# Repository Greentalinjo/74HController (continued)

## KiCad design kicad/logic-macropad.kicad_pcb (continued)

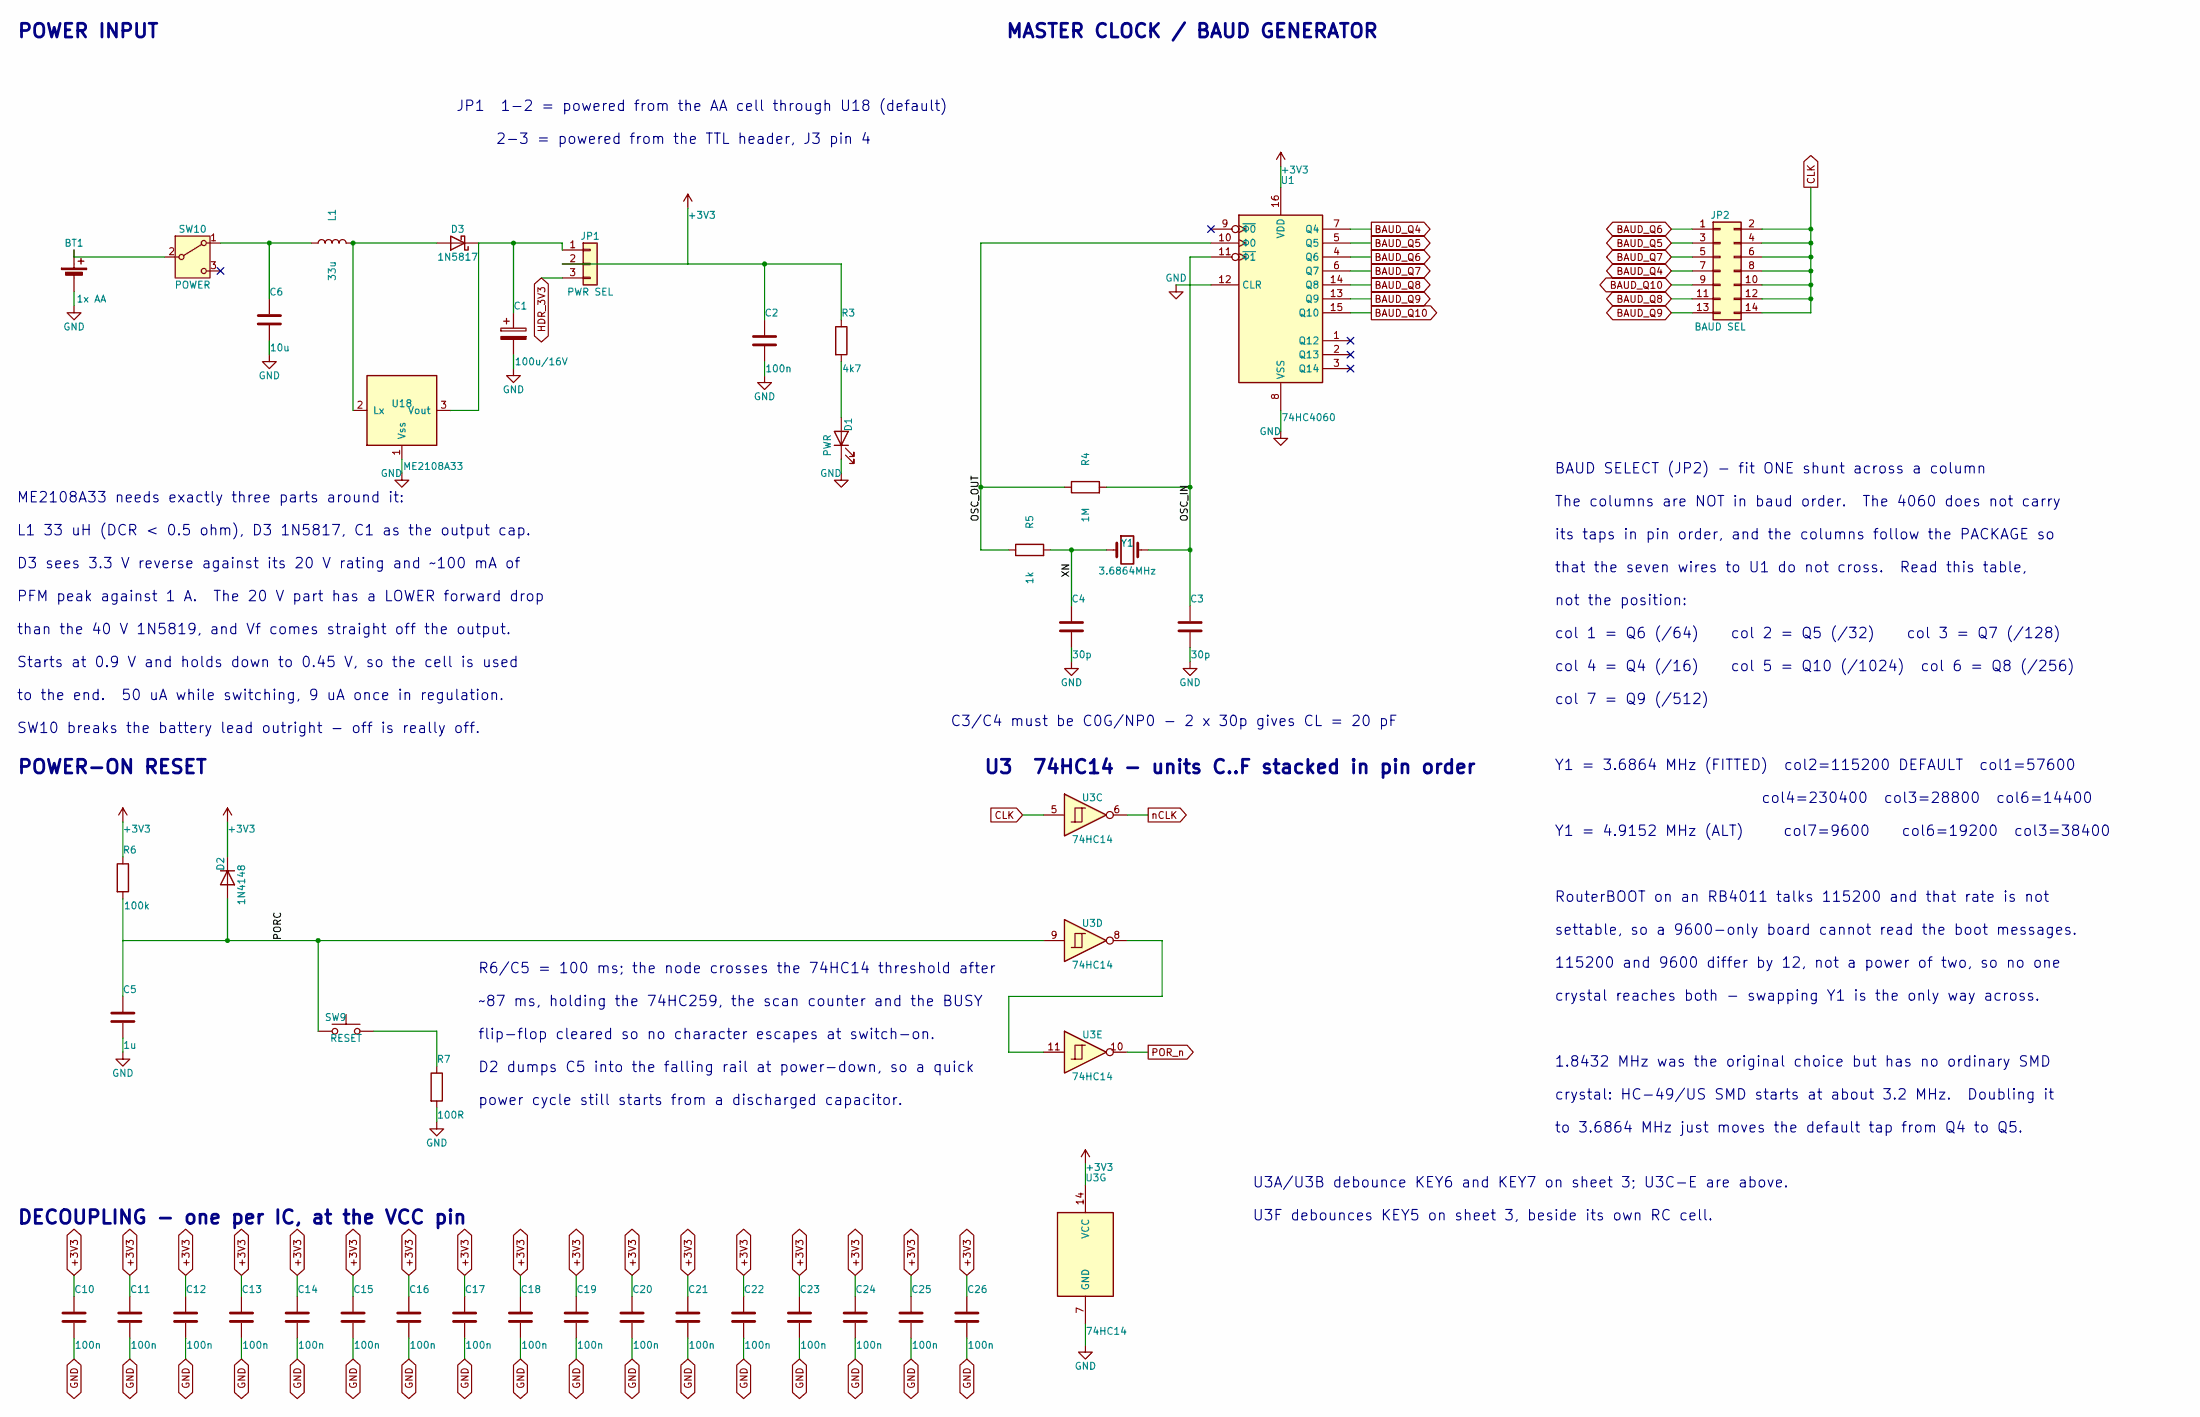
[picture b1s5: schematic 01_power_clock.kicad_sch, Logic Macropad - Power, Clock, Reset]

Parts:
BT1: 1x AA; BatteryHolder_MYOUNG_BH-AA-A1AJ020_1xAA; MPN BH-AA-A1AJ020
C1: 100u/16V; CP_Radial_D5.0mm_P2.00mm; MPN UVR1C101MED
C2, C10, C11, C12, C13, C14, C15, C16, C17, C18, C19, C20, C21, C22, C23, C24, C25, C26: 100n; C_0402_1005Metric; MPN GRM155R71H104KE14D
C3, C4: 30p; C_0402_1005Metric; MPN CC0402JRNPO9BN300
C5: 1u; C_0805_2012Metric; MPN GRM21BR71H105KA12L
C6: 10u; C_0805_2012Metric
D1: PWR; LED_0805_2012Metric_Pad1.15x1.40mm_HandSolder
D2: 1N4148; D_SOD-523; MPN 1N4148WT-7
D3: 1N5817; D_DO-41_SOD81_P10.16mm_Horizontal
JP1: PWR SEL; PinHeader_1x03_P2.54mm_Vertical; MPN 2.54-1*40P
JP2: BAUD SEL; PinHeader_2x07_P2.54mm_Vertical; MPN 2.54-2*7P
L1: 33u; L_Cenker_CKCS5040
R3: 4k7; R_0603_1608Metric
R4: 1M; R_0603_1608Metric
R5: 1k; R_0603_1608Metric
R6: 100k; R_0603_1608Metric
R7: 100R; R_0603_1608Metric
SW9: RESET; SW_PUSH_6mm; MPN K2-1102DP-F4SW-04
SW10: POWER; SW_Toggle_SPDT_ST-0-102; MPN ST-0-102-A01-T000-LF
U1: 74HC4060; SOIC-16_3.9x9.9mm_P1.27mm; MPN 74HC4060D
U3: 74HC14; SOIC-14_3.9x8.7mm_P1.27mm; MPN 74HC14D
U18: ME2108A33; SOT-23; MPN ME2108A33M3G
Y1: 3.6864MHz; Crystal_SMD_HC49-SD_HandSoldering; MPN ABLS-3.6864MHZ-B4-T

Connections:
+3V3: C2.1, C10.1, C11.1, C12.1, C13.1, C14.1, C15.1, C16.1, C17.1, C18.1, C19.1, C20.1, C21.1, C22.1, C23.1, C24.1, C25.1, C26.1, D2.1 (K), JP1.2, R3.1, R6.1, U1.16 (VDD), U3.14 (VCC); also elsewhere on the board
/Power, Clock, Reset/OSC_IN: C3.1, R4.2, U1.11 (~Φ1), Y1.2
/Power, Clock, Reset/OSC_OUT: R4.1, R5.1, U1.10 (Φ0)
/Power, Clock, Reset/PORC: C5.1, D2.2 (A), R6.2, SW9.1, U3.9
/Power, Clock, Reset/XN: C4.1, R5.2, Y1.1
BAUD_Q4: JP2.7, U1.7 (Q4)
BAUD_Q5: JP2.3, U1.5 (Q5)
BAUD_Q6: JP2.1, U1.4 (Q6)
BAUD_Q7: JP2.5, U1.6 (Q7)
BAUD_Q8: JP2.11, U1.14 (Q8)
BAUD_Q9: JP2.13, U1.13 (Q9)
BAUD_Q10: JP2.9, U1.15 (Q10)
CLK: JP2.2, JP2.4, JP2.6, JP2.8, JP2.10, JP2.12, JP2.14, U3.5; also elsewhere on the board
GND: BT1.2 (-), C1.2, C2.2, C3.2, C4.2, C5.2, C6.2, C10.2, C11.2, C12.2, C13.2, C14.2, C15.2, C16.2, C17.2, C18.2, C19.2, C20.2, C21.2, C22.2, C23.2, C24.2, C25.2, C26.2, D1.1 (K), R7.2, U1.8 (VSS), U1.12 (CLR), U3.7 (GND), U18.1 (Vss); also elsewhere on the board
HDR_3V3: JP1.3; also elsewhere on the board
unnamed: BT1.1 (+), SW10.2 (B)
unnamed: D1.2 (A), R3.2
unnamed: D3.2 (A), L1.2, U18.2 (Lx)
unnamed: C1.1, D3.1 (K), JP1.1, U18.3 (Vout)
unnamed: R7.1, SW9.2
unnamed: C6.1, L1.1, SW10.1 (A)
unnamed: U3.8, U3.11
POR_n: U3.10; also elsewhere on the board
nCLK: U3.6; also elsewhere on the board

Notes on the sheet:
flip-flop cleared so no character escapes at switch-on.
1.8432 MHz was the original choice but has no ordinary SMD
than the 40 V 1N5819, and Vf comes straight off the output.
col4=230400 col3=28800 col6=14400
settable, so a 9600-only board cannot read the boot messages.
Y1 = 3.6864 MHz (FITTED) col2=115200 DEFAULT col1=57600
crystal reaches both - swapping Y1 is the only way across.
POWER INPUT
The columns are NOT in baud order. The 4060 does not carry
col 4 = Q4 (/16) col 5 = Q10 (/1024) col 6 = Q8 (/256)
Starts at 0.9 V and holds down to 0.45 V, so the cell is used
its taps in pin order, and the columns follow the PACKAGE so
D3 sees 3.3 V reverse against its 20 V rating and ~100 mA of
R6/C5 = 100 ms; the node crosses the 74HC14 threshold after
not the position:
U3A/U3B debounce KEY6 and KEY7 on sheet 3; U3C-E are above.
col 7 = Q9 (/512)
2-3 = powered from the TTL header, J3 pin 4
BAUD SELECT (JP2) - fit ONE shunt across a column
Y1 = 4.9152 MHz (ALT) col7=9600 col6=19200 col3=38400
115200 and 9600 differ by 12, not a power of two, so no one
U3F debounces KEY5 on sheet 3, beside its own RC cell.
POWER-ON RESET
power cycle still starts from a discharged capacitor.
to the end. 50 uA while switching, 9 uA once in regulation.
PFM peak against 1 A. The 20 V part has a LOWER forward drop
U3 74HC14 - units C..F stacked in pin order
ME2108A33 needs exactly three parts around it:
C3/C4 must be C0G/NP0 - 2 x 30p gives CL = 20 pF
D2 dumps C5 into the falling rail at power-down, so a quick
MASTER CLOCK / BAUD GENERATOR
DECOUPLING - one per IC, at the VCC pin
to 3.6864 MHz just moves the default tap from Q4 to Q5.
SW10 breaks the battery lead outright - off is really off.
RouterBOOT on an RB4011 talks 115200 and that rate is not
JP1 1-2 = powered from the AA cell through U18 (default)
L1 33 uH (DCR < 0.5 ohm), D3 1N5817, C1 as the output cap.
that the seven wires to U1 do not cross. Read this table,
col 1 = Q6 (/64) col 2 = Q5 (/32) col 3 = Q7 (/128)
crystal: HC-49/US SMD starts at about 3.2 MHz. Doubling it

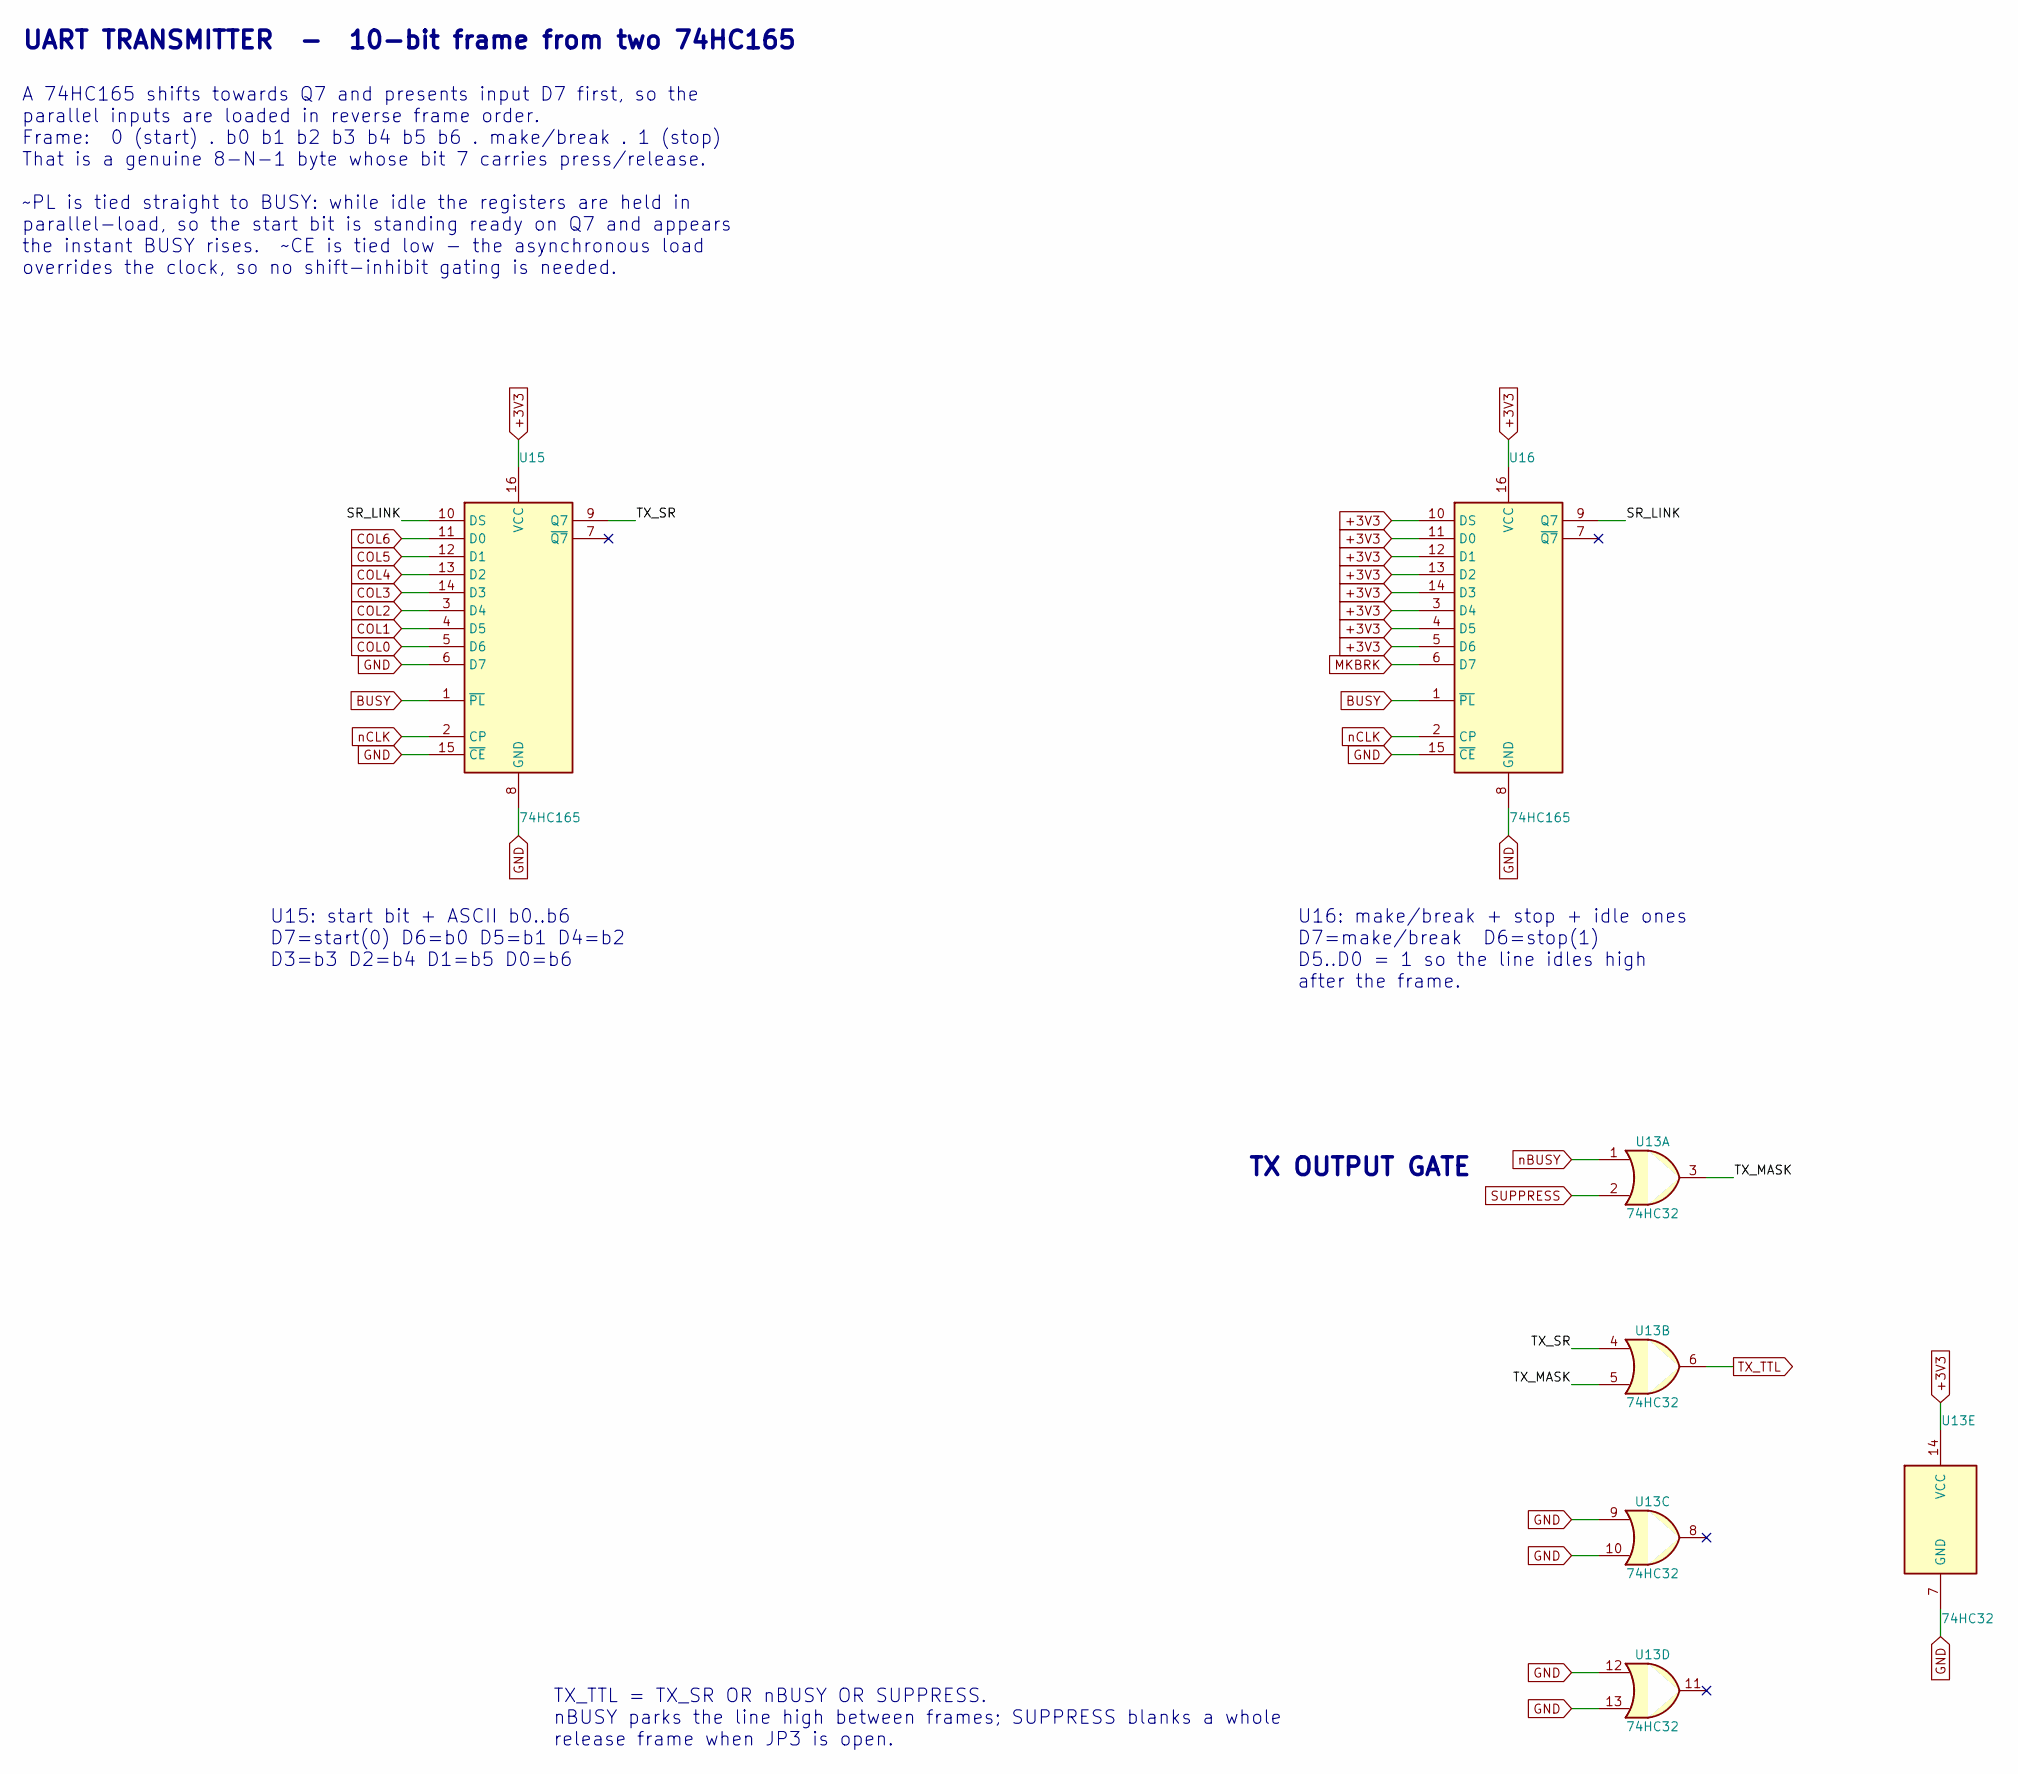
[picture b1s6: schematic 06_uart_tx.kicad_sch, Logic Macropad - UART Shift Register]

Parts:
U13: 74HC32; SOIC-14_3.9x8.7mm_P1.27mm; MPN 74HC32D
U15, U16: 74HC165; SOIC-16_3.9x9.9mm_P1.27mm; MPN 74HC165D

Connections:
+3V3: U13.14 (VCC), U15.16 (VCC), U16.3 (D4), U16.4 (D5), U16.5 (D6), U16.10 (DS), U16.11 (D0), U16.12 (D1), U16.13 (D2), U16.14 (D3), U16.16 (VCC); also elsewhere on the board
/UART Shift Register/SR_LINK: U15.10 (DS), U16.9 (Q7)
/UART Shift Register/TX_MASK: U13.3, U13.5
/UART Shift Register/TX_SR: U13.4, U15.9 (Q7)
BUSY: U15.1 (~PL), U16.1 (~PL); also elsewhere on the board
COL0: U15.5 (D6); also elsewhere on the board
COL1: U15.4 (D5); also elsewhere on the board
COL2: U15.3 (D4); also elsewhere on the board
COL3: U15.14 (D3); also elsewhere on the board
COL4: U15.13 (D2); also elsewhere on the board
COL5: U15.12 (D1); also elsewhere on the board
COL6: U15.11 (D0); also elsewhere on the board
GND: U13.7 (GND), U13.9, U13.10, U13.12, U13.13, U15.6 (D7), U15.8 (GND), U15.15 (~CE), U16.8 (GND), U16.15 (~CE); also elsewhere on the board
MKBRK: U16.6 (D7); also elsewhere on the board
SUPPRESS: U13.2; also elsewhere on the board
TX_TTL: U13.6; also elsewhere on the board
nBUSY: U13.1; also elsewhere on the board
nCLK: U15.2 (CP), U16.2 (CP); also elsewhere on the board

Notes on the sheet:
A 74HC165 shifts towards Q7 and presents input D7 first, so the parallel inputs are loaded in reverse frame order. Frame: 0 (start) . b0 b1 b2 b3 b4 b5 b6 . make/break . 1 (stop) That is a genuine 8-N-1 byte whose bit 7 carries press/release. ~PL is tied straight to BUSY: while idle the registers a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
UART TRANSMITTER - 10-bit frame from two 74HC165
TX_TTL = TX_SR OR nBUSY OR SUPPRESS. nBUSY parks the line high between frames; SUPPRESS blanks a whole release frame when JP3 is open.
U15: start bit + ASCII b0..b6 D7=start(0) D6=b0 D5=b1 D4=b2 D3=b3 D2=b4 D1=b5 D0=b6
U16: make/break + stop + idle ones D7=make/break D6=stop(1) D5..D0 = 1 so the line idles high after the frame.
TX OUTPUT GATE

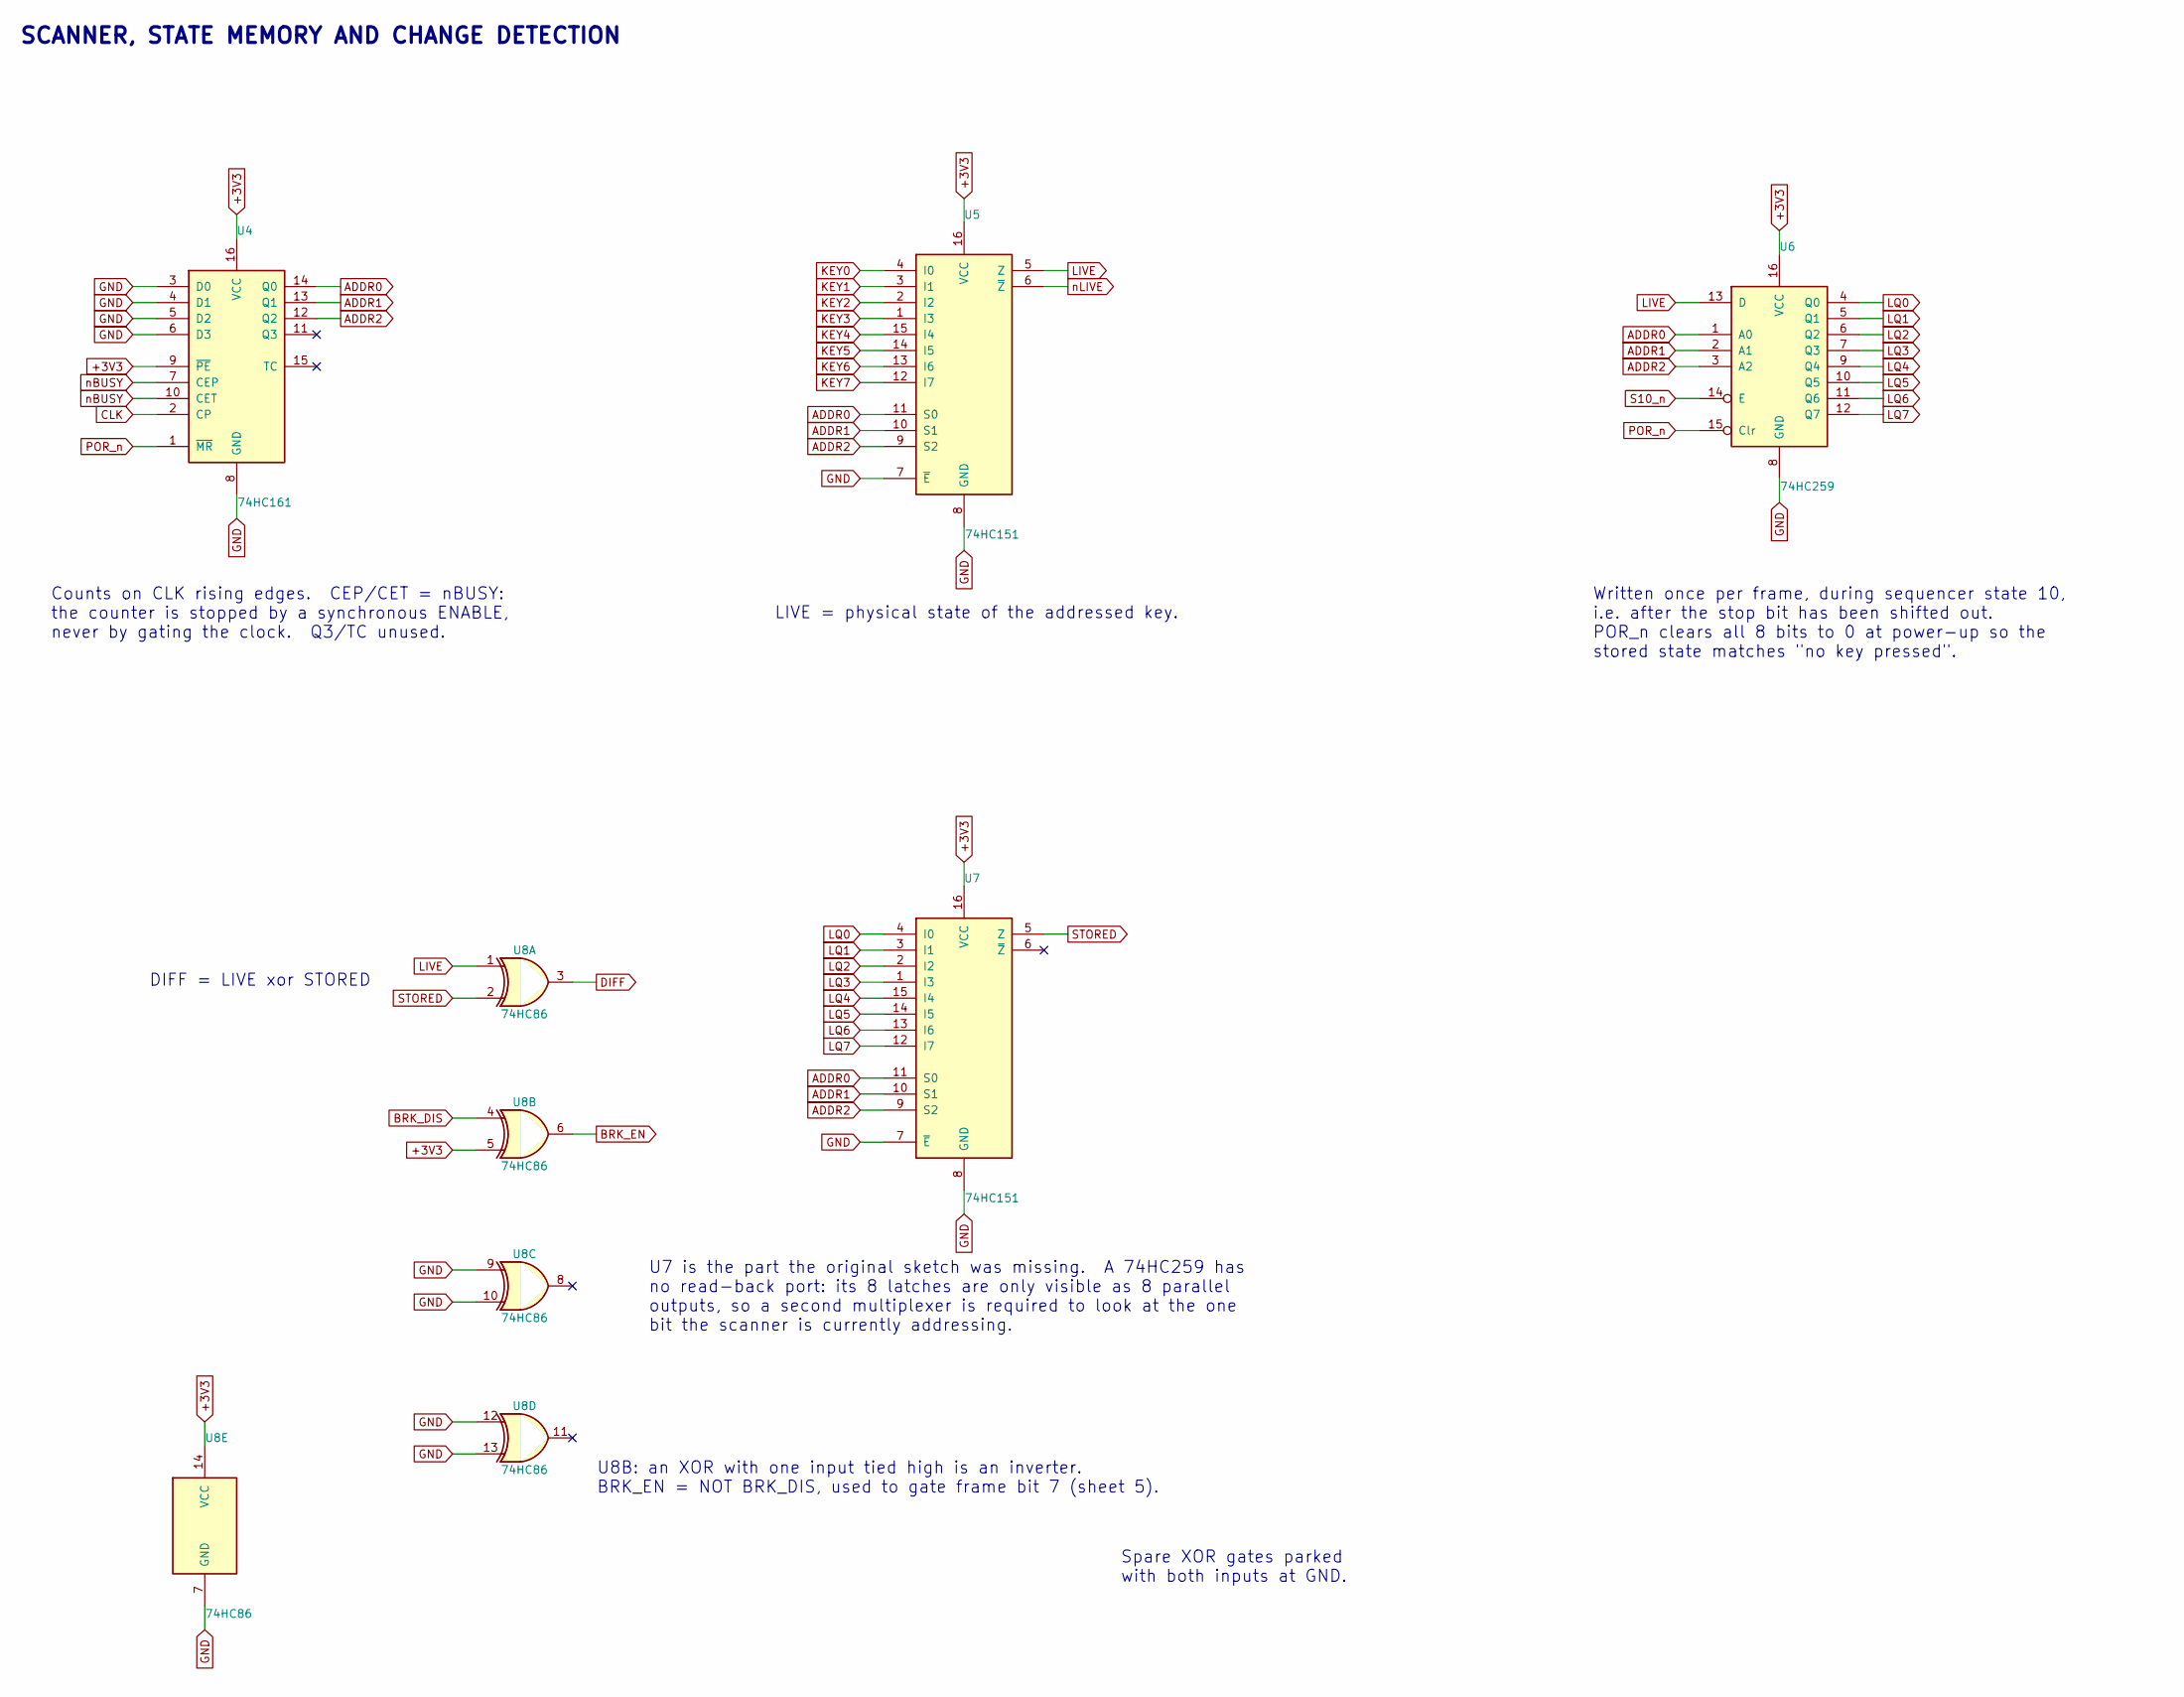
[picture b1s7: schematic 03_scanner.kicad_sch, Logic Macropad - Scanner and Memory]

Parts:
U4: 74HC161; SOIC-16_3.9x9.9mm_P1.27mm; MPN 74HC161D
U5, U7: 74HC151; SOIC-16_3.9x9.9mm_P1.27mm; MPN 74HC151D
U6: 74HC259; SOIC-16_3.9x9.9mm_P1.27mm; MPN 74HC259D
U8: 74HC86; SOIC-14_3.9x8.7mm_P1.27mm; MPN 74HC86D

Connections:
+3V3: U4.9 (~PE), U4.16 (VCC), U5.16 (VCC), U6.16 (VCC), U7.16 (VCC), U8.5, U8.14 (VCC); also elsewhere on the board
ADDR0: U4.14 (Q0), U5.11 (S0), U6.1 (A0), U7.11 (S0); also elsewhere on the board
ADDR1: U4.13 (Q1), U5.10 (S1), U6.2 (A1), U7.10 (S1); also elsewhere on the board
ADDR2: U4.12 (Q2), U5.9 (S2), U6.3 (A2), U7.9 (S2); also elsewhere on the board
BRK_DIS: U8.4; also elsewhere on the board
BRK_EN: U8.6; also elsewhere on the board
CLK: U4.2 (CP); also elsewhere on the board
DIFF: U8.3; also elsewhere on the board
GND: U4.3 (D0), U4.4 (D1), U4.5 (D2), U4.6 (D3), U4.8 (GND), U5.7 (~E), U5.8 (GND), U6.8 (GND), U7.7 (~E), U7.8 (GND), U8.7 (GND), U8.9, U8.10, U8.12, U8.13; also elsewhere on the board
KEY0: U5.4 (I0); also elsewhere on the board
KEY1: U5.3 (I1); also elsewhere on the board
KEY2: U5.2 (I2); also elsewhere on the board
KEY3: U5.1 (I3); also elsewhere on the board
KEY4: U5.15 (I4); also elsewhere on the board
KEY5: U5.14 (I5); also elsewhere on the board
KEY6: U5.13 (I6); also elsewhere on the board
KEY7: U5.12 (I7); also elsewhere on the board
LIVE: U5.5 (Z), U6.13 (D), U8.1; also elsewhere on the board
LQ0: U6.4 (Q0), U7.4 (I0)
LQ1: U6.5 (Q1), U7.3 (I1)
LQ2: U6.6 (Q2), U7.2 (I2)
LQ3: U6.7 (Q3), U7.1 (I3)
LQ4: U6.9 (Q4), U7.15 (I4)
LQ5: U6.10 (Q5), U7.14 (I5)
LQ6: U6.11 (Q6), U7.13 (I6)
LQ7: U6.12 (Q7), U7.12 (I7)
POR_n: U4.1 (~MR), U6.15 (Clr); also elsewhere on the board
S10_n: U6.14 (E); also elsewhere on the board
STORED: U7.5 (Z), U8.2
nBUSY: U4.7 (CEP), U4.10 (CET); also elsewhere on the board
nLIVE: U5.6 (~Z); also elsewhere on the board

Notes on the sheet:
LIVE = physical state of the addressed key.
DIFF = LIVE xor STORED
Spare XOR gates parked with both inputs at GND.
Counts on CLK rising edges. CEP/CET = nBUSY: the counter is stopped by a synchronous ENABLE, never by gating the clock. Q3/TC unused.
U8B: an XOR with one input tied high is an inverter. BRK_EN = NOT BRK_DIS, used to gate frame bit 7 (sheet 5).
SCANNER, STATE MEMORY AND CHANGE DETECTION
U7 is the part the original sketch was missing. A 74HC259 has no read-back port: its 8 latches are only visible as 8 parallel outputs, so a second multiplexer is required to look at the one bit the scanner is currently addressing.
Written once per frame, during sequencer state 10, i.e. after the stop bit has been shifted out. POR_n clears all 8 bits to 0 at power-up so the stored state matches "no key pressed".

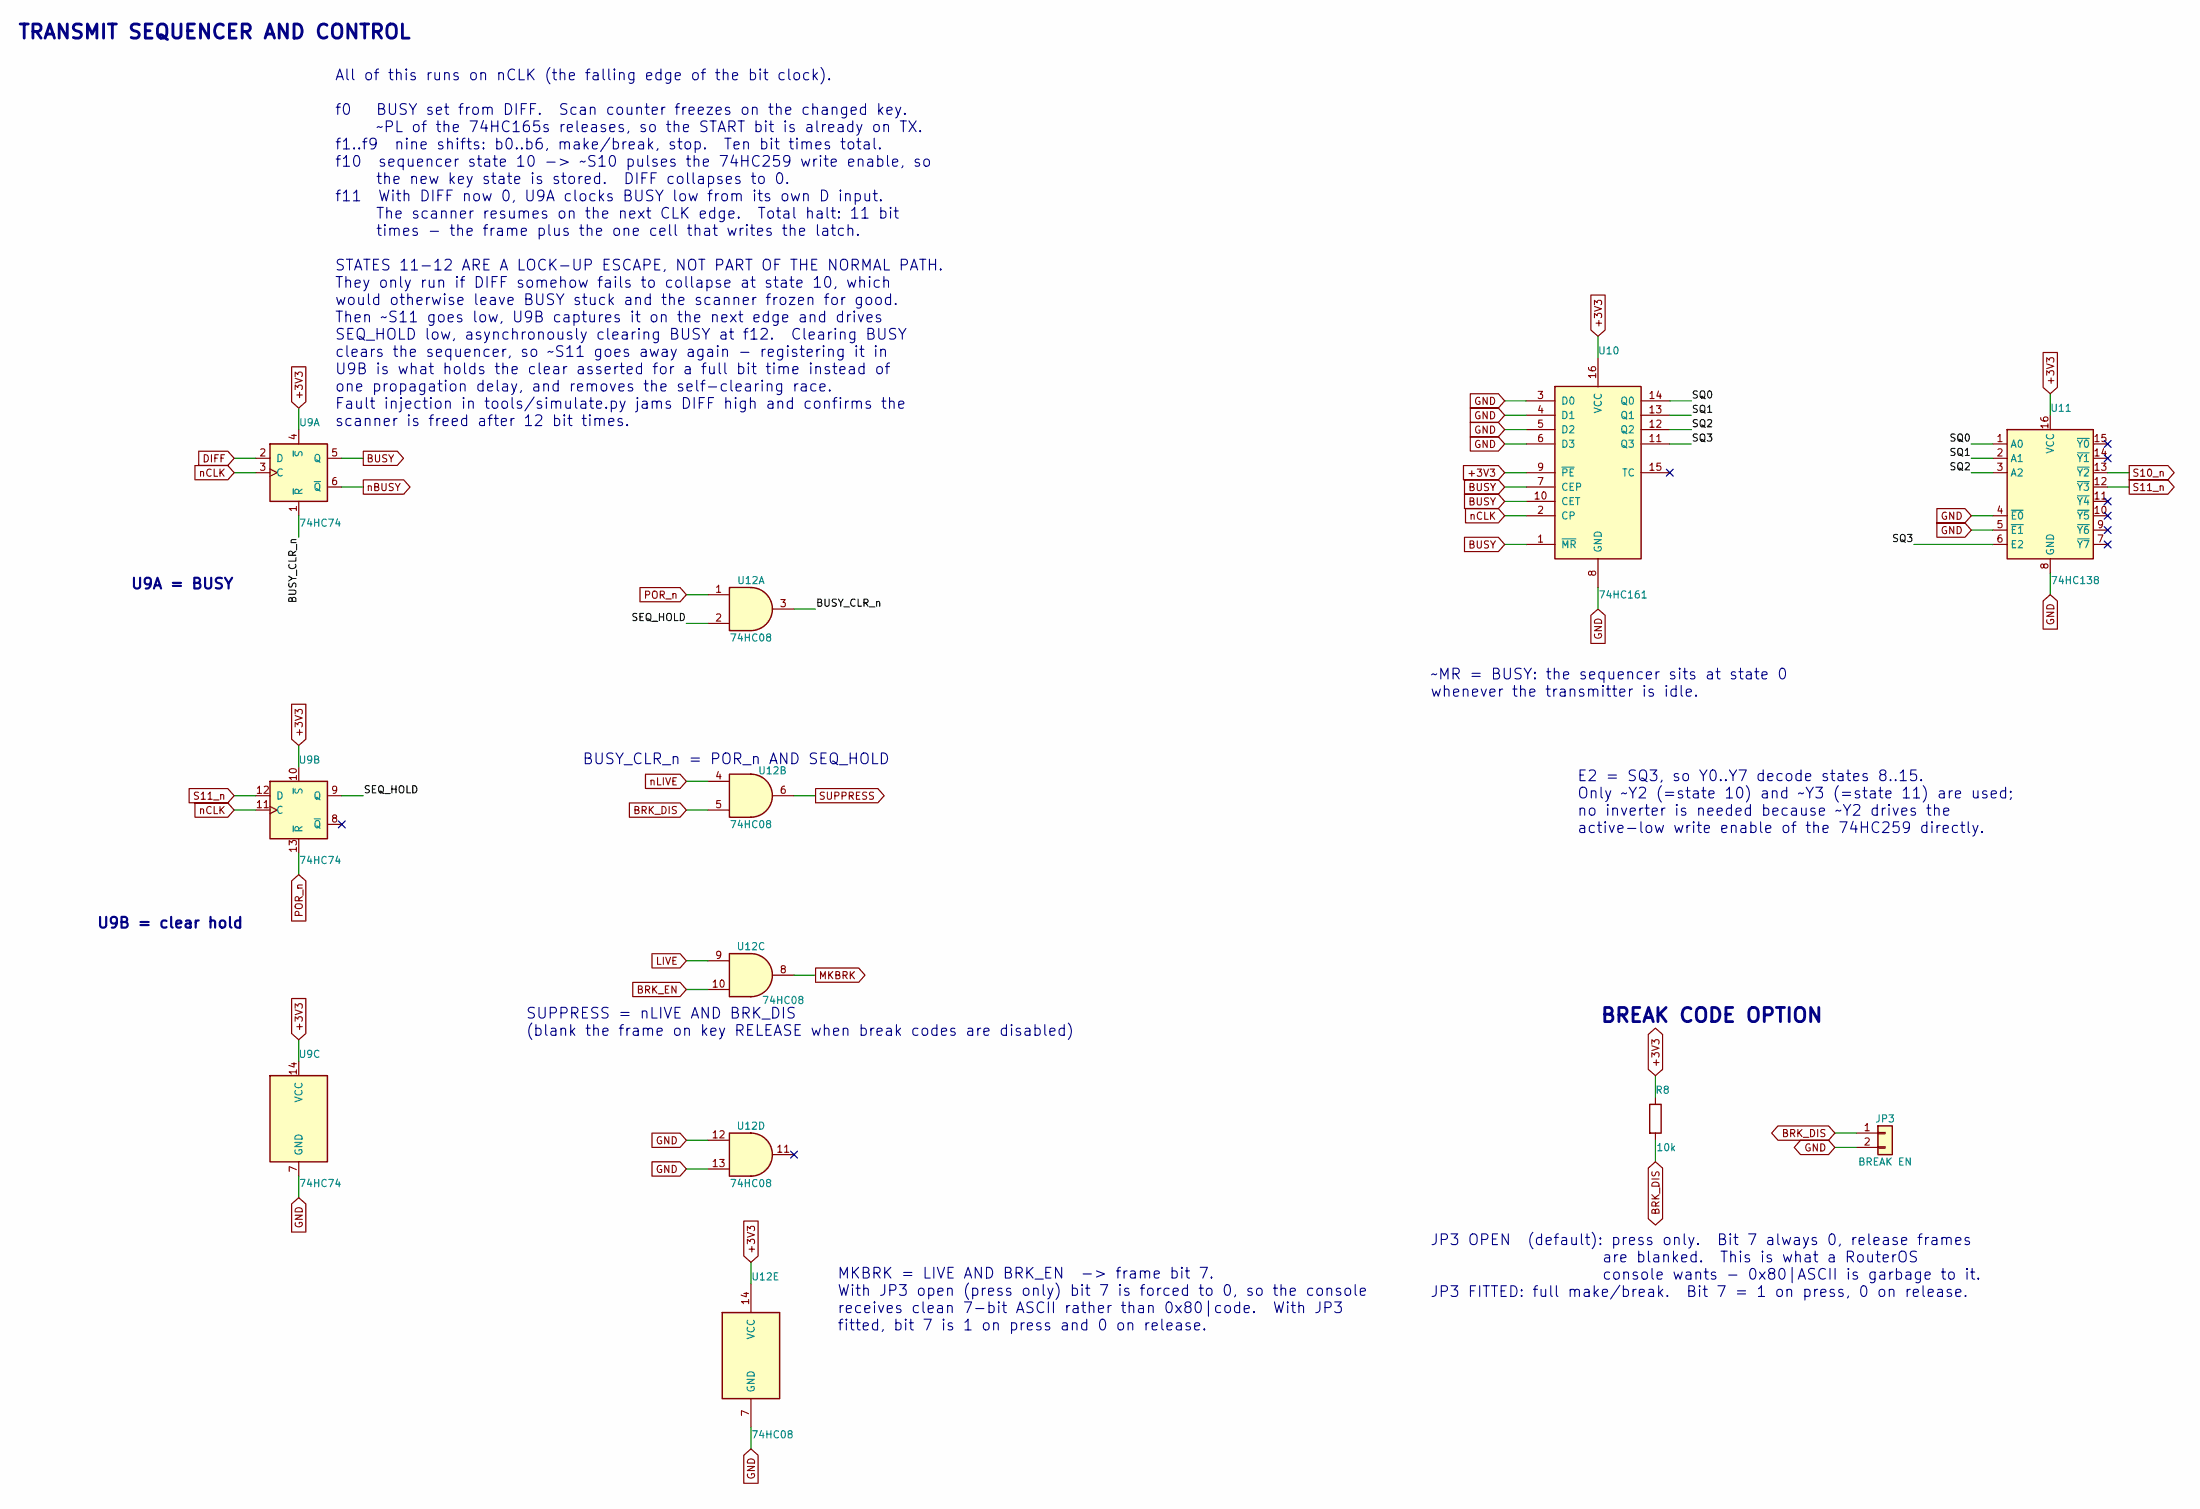
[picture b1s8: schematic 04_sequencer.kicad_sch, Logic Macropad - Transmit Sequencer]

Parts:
JP3: BREAK EN; PinHeader_1x02_P2.54mm_Vertical; MPN 2.54-1*40P
R8: 10k; R_0603_1608Metric
U9: 74HC74; SOIC-14_3.9x8.7mm_P1.27mm; MPN 74HC74D
U10: 74HC161; SOIC-16_3.9x9.9mm_P1.27mm; MPN 74HC161D
U11: 74HC138; SOIC-16_3.9x9.9mm_P1.27mm; MPN 74HC138D
U12: 74HC08; SOIC-14_3.9x8.7mm_P1.27mm; MPN 74HC08D

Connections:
+3V3: R8.1, U9.4 (~S), U9.10 (~S), U9.14 (VCC), U10.9 (~PE), U10.16 (VCC), U11.16 (VCC), U12.14 (VCC); also elsewhere on the board
/Transmit Sequencer/BUSY_CLR_n: U9.1 (~R), U12.3
/Transmit Sequencer/SEQ_HOLD: U9.9 (Q), U12.2
/Transmit Sequencer/SQ0: U10.14 (Q0), U11.1 (A0)
/Transmit Sequencer/SQ1: U10.13 (Q1), U11.2 (A1)
/Transmit Sequencer/SQ2: U10.12 (Q2), U11.3 (A2)
/Transmit Sequencer/SQ3: U10.11 (Q3), U11.6 (E2)
BRK_DIS: JP3.1, R8.2, U12.5; also elsewhere on the board
BRK_EN: U12.10; also elsewhere on the board
BUSY: U9.5 (Q), U10.1 (~MR), U10.7 (CEP), U10.10 (CET); also elsewhere on the board
DIFF: U9.2 (D); also elsewhere on the board
GND: JP3.2, U9.7 (GND), U10.3 (D0), U10.4 (D1), U10.5 (D2), U10.6 (D3), U10.8 (GND), U11.4 (~E0), U11.5 (~E1), U11.8 (GND), U12.7 (GND), U12.12, U12.13; also elsewhere on the board
LIVE: U12.9; also elsewhere on the board
MKBRK: U12.8; also elsewhere on the board
POR_n: U9.13 (~R), U12.1; also elsewhere on the board
S10_n: U11.13 (~Y2); also elsewhere on the board
S11_n: U9.12 (D), U11.12 (~Y3)
SUPPRESS: U12.6; also elsewhere on the board
nBUSY: U9.6 (~Q); also elsewhere on the board
nCLK: U9.3 (C), U9.11 (C), U10.2 (CP); also elsewhere on the board
nLIVE: U12.4; also elsewhere on the board

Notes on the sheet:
BREAK CODE OPTION
~MR = BUSY: the sequencer sits at state 0 whenever the transmitter is idle.
MKBRK = LIVE AND BRK_EN -> frame bit 7. With JP3 open (press only) bit 7 is forced to 0, so the console receives clean 7-bit ASCII rather than 0x80|code. With JP3 fitted, bit 7 is 1 on press and 0 on release.
All of this runs on nCLK (the falling edge of the bit clock). f0 BUSY set from DIFF. Scan counter freezes on the changed key. ~PL of the 74HC165s releases, so the START bit is already on TX. f1..f9 nine shifts: b0..b6, make/break, stop. Ten bit times total. f10 sequencer state 10 -> ~S10 pulses the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
SUPPRESS = nLIVE AND BRK_DIS (blank the frame on key RELEASE when break codes are disabled)
TRANSMIT SEQUENCER AND CONTROL
JP3 OPEN (default): press only. Bit 7 always 0, release frames are blanked. This is what a RouterOS console wants - 0x80|ASCII is garbage to it. JP3 FITTED: full make/break. Bit 7 = 1 on press, 0 on release.
U9B = clear hold
U9A = BUSY
BUSY_CLR_n = POR_n AND SEQ_HOLD
E2 = SQ3, so Y0..Y7 decode states 8..15. Only ~Y2 (=state 10) and ~Y3 (=state 11) are used; no inverter is needed because ~Y2 drives the active-low write enable of the 74HC259 directly.

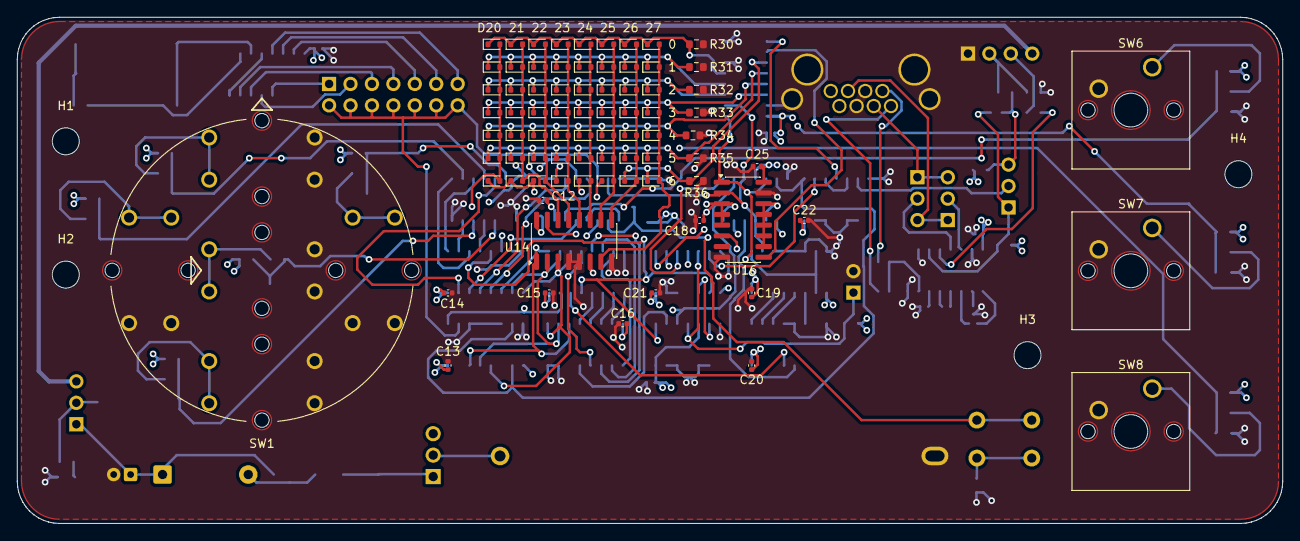
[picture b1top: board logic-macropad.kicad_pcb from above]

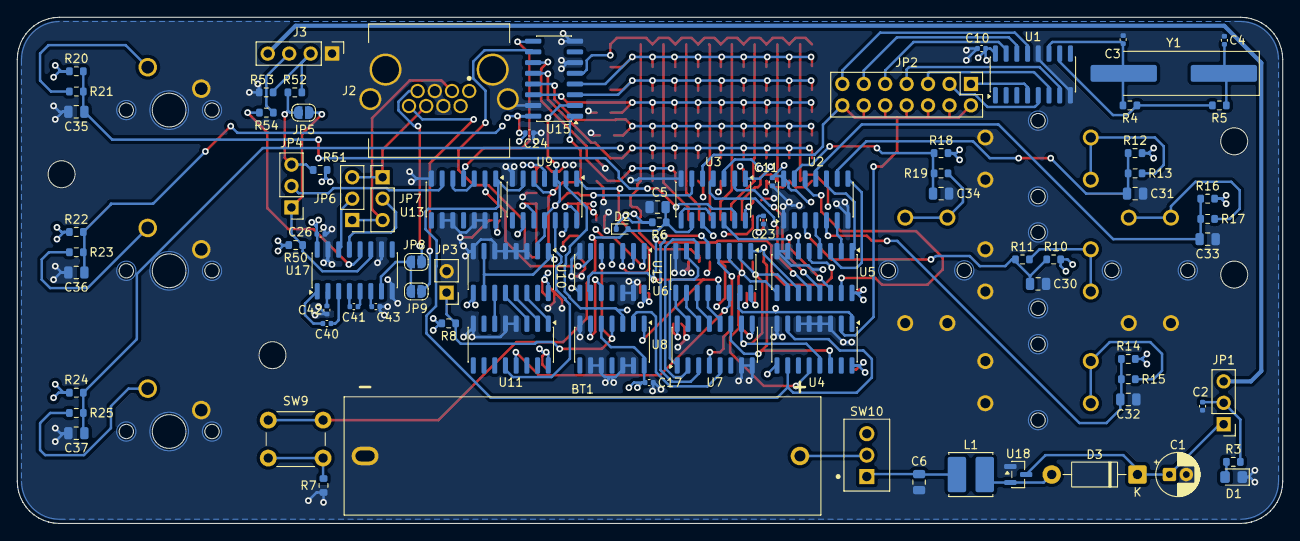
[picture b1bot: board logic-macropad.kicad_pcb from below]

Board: 6 copper layers, 150.0 x 60.0 mm, 170 parts (86 on the bottom side), 114 nets.

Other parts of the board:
H1, H2, H3, H4: M3; MountingHole_3.2mm_M3
